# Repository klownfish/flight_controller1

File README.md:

The goal for the flight controller is to

1. Measure acceleration, rotation and altitude
1. Get rocket location
1. Store all measurements on-board
1. Real-time telemetry
1. Ignite explosive charges
1. Record video

So far it has been used on [rocket1](https://github.com/klownfish/rocket1) and my W.I.P guided rocket.

### Sensors

The altitude is calculated from the pressure using a BMP280 pressure sensor. The accuracy is about +-1m which is good enough for determining the apogee but acceleration and velocity is pretty much completely lost in the noise. Acceleration and rotation is gathered from a MPU9250 which sucks hard unfortunately. The gyroscope drifts rapidly and so there is no way to get the an accurate attitude estimate. Both of these sensors are available on a GY-91 breakout board.

A Ublox M8 GPS from Team Blacksheep measured the location. The Ublox chip is easy to configure and use but the module I chose does not have any moutning holes…

### Telemetry
All data is stored on a Winond NOR flash IC and it does what it’s supposed to do. I wanted to use a RF96 LoRa modem but I mixed up the numbers ordered a RF69 generic GFSK modem. It works alright so it didn’t really matter in the end. I have not conducted a real range test but the “GFSK_Rb38_4Fd76_8” profile worked for my 30m launches.

### Pyro channels
The pyro channels consist of half H-bridges connected to GND and 12V. A half bridge is necessary to keep the channel shorted when not in use. A TVS diode is connected in parallel as well to protect from electrostatic discarges. BTN7030-1EPA is an awesome “smart” half bridge IC and powers all the channels. It has built in short circuit and overheat protection. It can source 14 Amps of currents which is on the low side for what I want to do. Running of a 3s LiPo battery at 12.6v it can power a 1.1 Ohm load which is very close to the resistance of an ignitor. From empirical data it has worked four out four times so far.

As an additional safety measure a jumper can overwrite the logic output from the micro controller and force all enable pins low. Two LEDs also show if the channels are armed or not.

### Video
A runcam split 4 recorded the onboard footage and I can not recommend it. The auto record function just straight up does not work so it doesn’t record on start up. As a result you have to push a button to start the recording manually and good luck doing that when it’s mounted inside a nose cone. Good thing the camera only cost 80€ and was destroyed in a crash. I hate that camera so fucking much I am so mad AAAAAAHHH

### Guidance
This flight controller is currently the base for a guided rocket that i am developing. It's possible to connect a BMI088 IMU to the expansion port which is much more accurate than the MPU9250. The UART pins for the GPS can also be used to control 2 servos. The servos are connected to a pyro channel with an external voltage regulator.

### Dashboard
The dashboard is written in python using TK and Matplotlib.

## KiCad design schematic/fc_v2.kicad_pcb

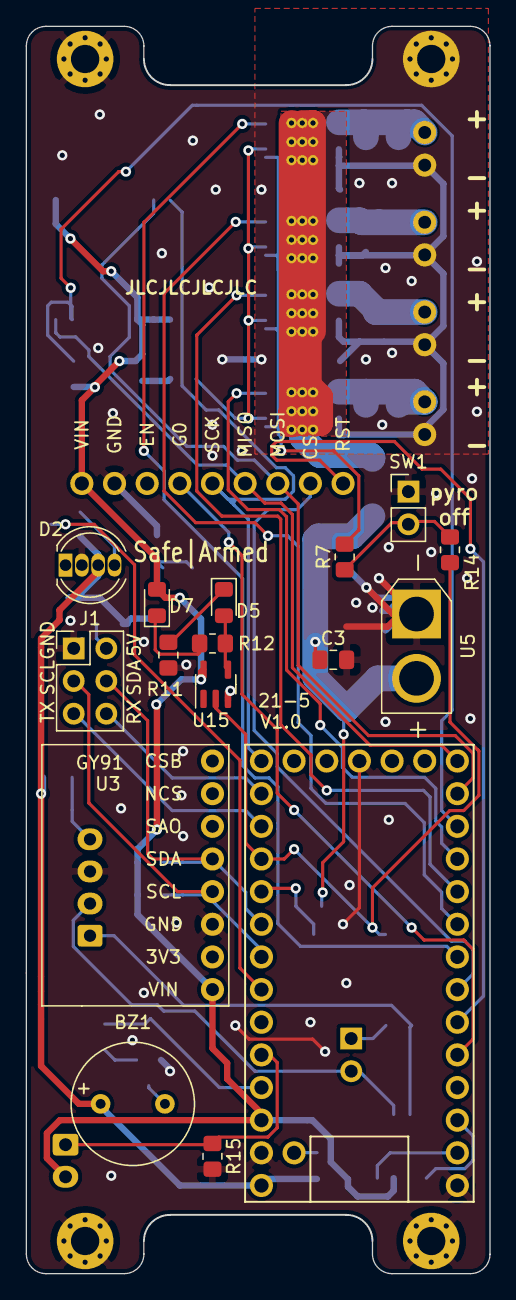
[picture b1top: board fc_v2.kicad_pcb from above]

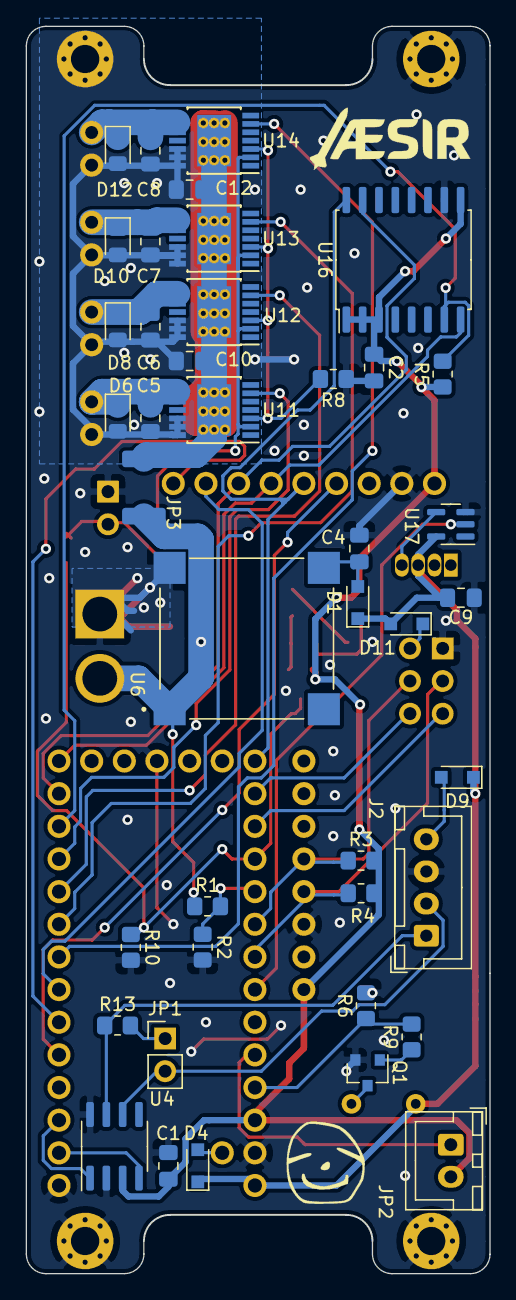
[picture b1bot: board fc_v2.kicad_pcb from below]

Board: 2 copper layers, 36.0 x 97.0 mm, 68 parts (47 on the bottom side), 47 nets.

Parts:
BZ1: Buzzer; CX-0905C
C1, C5, C6, C7, C8, C9, C10, C12: 100n; C_0805_2012Metric_Pad1.18x1.45mm_HandSolder
C2: 100p; C_0805_2012Metric_Pad1.18x1.45mm_HandSolder
C3: 20u; C_0805_2012Metric_Pad1.18x1.45mm_HandSolder
C4: 10u; C_0805_2012Metric_Pad1.18x1.45mm_HandSolder
D1, D4, D9, D11: D_Schottky; D_SOD-323_HandSoldering
D2: WS2812B; ws2812-through-hole-5mm
D5: ARMED; LED_0805_2012Metric_Pad1.15x1.40mm_HandSolder
D6, D8, D10, D12: D_TVS; D_0805_2012Metric_Pad1.15x1.40mm_HandSolder
D7: SAFE; LED_0805_2012Metric_Pad1.15x1.40mm_HandSolder
H1, H2, H4, H5: MountingHole_Pad; MountingHole_2.2mm_M2_Pad_Via
H3: Logo; avatar
H6: Aesir; aesir
J1: Conn_02x03_Odd_Even; PinHeader_2x03_P2.54mm_Vertical
J2: JST_XH_4; JST_XH_B4B-XH-A_1x04_P2.50mm_Vertical
JP1: Jumper_NC_Small; PinHeader_1x02_P2.54mm_Vertical
JP2: Jumper; JST_XH_B2B-XH-A_1x02_P2.50mm_Vertical
JP3: Jumper_NO_Small; R_1812_4532Metric_Pad1.30x3.40mm_HandSolder_no_silk
Q1: MMBT3904; SOT-23
R1: 6.04k; R_0805_2012Metric_Pad1.20x1.40mm_HandSolder
R2, R15: 2k; R_0805_2012Metric_Pad1.20x1.40mm_HandSolder
R3, R4, R10: 4.7k; R_0805_2012Metric_Pad1.20x1.40mm_HandSolder
R5, R6, R8: 10k; R_0805_2012Metric_Pad1.20x1.40mm_HandSolder
R7, R9, R14: 1k; R_0805_2012Metric_Pad1.20x1.40mm_HandSolder
R11, R12: 400; R_0805_2012Metric_Pad1.20x1.40mm_HandSolder
R13: 120; R_0805_2012Metric_Pad1.20x1.40mm_HandSolder
SW1: SW_DPST_x2; PinHeader_1x02_P2.54mm_Vertical
U1: teensy4
U2: RFM69HCW; Adafruit-RFM69
U3: GY91
U4: SN65HVD230; SOIC-8_3.9x4.9mm_P1.27mm
U5: xt-30; AMASS_XT30U-M_1x02_P5.0mm_Vertical
U6: VXO7805-500-M
U7, U8, U9, U10: terminal-2; terminal-small
U11, U12, U13, U14: BTN7030-1EPA; Infineon_PG-TSDSO-14-22-bottom
U15, U17: NL17SZ17; SC-74-a
U16: w25nxx; SOIC-16W_7.5x10.3mm_P1.27mm

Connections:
3V3: C1.2, C2.1, D7.2, JP2.2, R3.2, R4.2, R5.1, U1.31, U2.1, U3.1, U4.3, U15.5, U16.1, U16.2, U16.3, U16.9
5V: BZ1.1, C9.1, D1.1, D2.3, D4.1, D9.1, D11.2, U1.33, U17.5
12V: C3.1, JP3.1, R1.1, U5.2, U6.1
12V_LIMIT: C10.2, C12.2, JP3.2, U11.15, U12.15, U13.15, U14.15
/BAT_READ: R1.2, R2.1, U1.24
/BUZZ: R6.1, R9.2, U1.30
/CAN_RX: U1.2, U4.4
/CAN_TX: U1.3, U4.1
/EXT_RX: J1.6, U1.21
/EXT_TX: J1.5, U1.22
/FLASH_CS: R5.2, U1.12, U16.7
/LIFTOFF: JP2.1, R15.1, U1.29
/MISO: U1.14, U2.6, U16.8
/MOSI: U1.13, U2.7, U16.15
/P_EN: R7.2, U11.2, U12.2, U13.2, U14.2
/P_IN_1: U1.11, U11.6
/P_IN_2: U1.10, U12.6
/P_IN_3: U1.9, U13.6
/P_IN_4: U1.8, U14.6
/RF_CS: U1.7, U2.8
/RF_G0: U1.5, U2.4
/RF_RST: U1.6, U2.9
/RGB_TX: U1.27, U17.2
/SCK: U1.20, U2.5, U16.16
/SCL: J1.3, R4.1, U1.26, U3.4
/SDA: J1.4, R3.1, U1.25, U3.5
/UNSAFE_P_EN: R10.1, R14.1, U1.23, U15.2
GND: C1.1, C2.2, C3.2, C4.2, C5.1, C6.1, C7.1, C8.1, C9.2, C10.1, C12.1, D2.1, D6.2, D8.2, D10.2, D12.2, H1.1, H2.1, H4.1, H5.1, J1.1, J2.3, Q1.2, R2.2, R6.2, R8.1, R10.2, R11.1, R15.2, SW1.1, U1.1, U1.17, U1.32, U2.2, U3.3, U4.2, U4.8, U5.1, U6.2, U7.1, U8.1, U9.1, U10.1, U11.12, U11.13, U11.14, U12.12, U12.13, U12.14, U13.12, U13.13, U13.14, U14.12, U14.13, U14.14, U15.3, U16.10, U17.3
unnamed: BZ1.2, Q1.3
unnamed: C4.1, D1.2, U6.3
unnamed: C5.2, D6.1, U7.2, U11.8, U11.9, U11.10
unnamed: C6.2, D8.1, U8.2, U12.8, U12.9, U12.10
unnamed: C7.2, D10.1, U9.2, U13.8, U13.9, U13.10
unnamed: C8.2, D12.1, U10.2, U14.8, U14.9, U14.10
unnamed: D2.4, U17.4
unnamed: D4.2, U1.34
unnamed: D5.1, R11.2
unnamed: D5.2, R12.2, U15.4
unnamed: D7.1, R12.1
unnamed: D9.2, J2.4
unnamed: D11.1, J1.2
unnamed: J2.1, R13.1, U4.7
unnamed: J2.2, JP1.2, U4.6
unnamed: JP1.1, R13.2
unnamed: Q1.1, R9.1
unnamed: R8.2, U11.3, U12.3, U13.3, U14.3
unnamed: R7.1, R14.2, SW1.2

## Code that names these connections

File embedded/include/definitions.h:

#if __has_include("callsign.h")
#   include "callsign.h"
#   define TX_POWER 20
#   define IS_HAM true
#else
#   define CALLSIGN ""
#   define TX_POWER 13
#   define IS_HAM false
#endif

#define RADIO_BUF_LEN 128

#define RADIO_FREQUENCY 433.800
#define MODULATION RH_RF69::ModemConfigChoice::GFSK_Rb38_4Fd76_8

#define PIN_CAN_RX 0
#define PIN_CAN_RX 1
#define PIN_RF_G0 3
#define PIN_RF_RST 4
#define PIN_RF_CS 5
#define PIN_PYRO_4 6
#define PIN_PYRO_3 7
#define PIN_PYRO_2 8
#define PIN_PYRO_1 9
#define PIN_FLASH_CS 10
#define PIN_MOSI 11
#define PIN_MISO 12
#define PIN_SCK 13
#define PIN_EXT_RX 14
#define PIN_EXT_TX 15
#define PIN_PYRO_ARM 16
#define PIN_BAT_READ 17
#define PIN_SDA 18
#define PIN_SCL 19
#define PIN_RGB_TX 20
#define PIN_LIFTOFF 22
#define PIN_BUZZER 23

#define RED    0x160000
#define GREEN  0x001600
#define BLUE   0x000016
#define YELLOW 0x101400
#define PINK   0x120009
#define ORANGE 0x100400
#define WHITE  0x101010

#define BAUD 115200

#define BUZZER_HZ 2700

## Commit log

2021-11-08 guidance W.I.P
2021-11-23 better structure
2021-12-24 pre async rewrite
2021-12-31 yiedling rewrite
2022-01-01 updated protocol and dashboard
